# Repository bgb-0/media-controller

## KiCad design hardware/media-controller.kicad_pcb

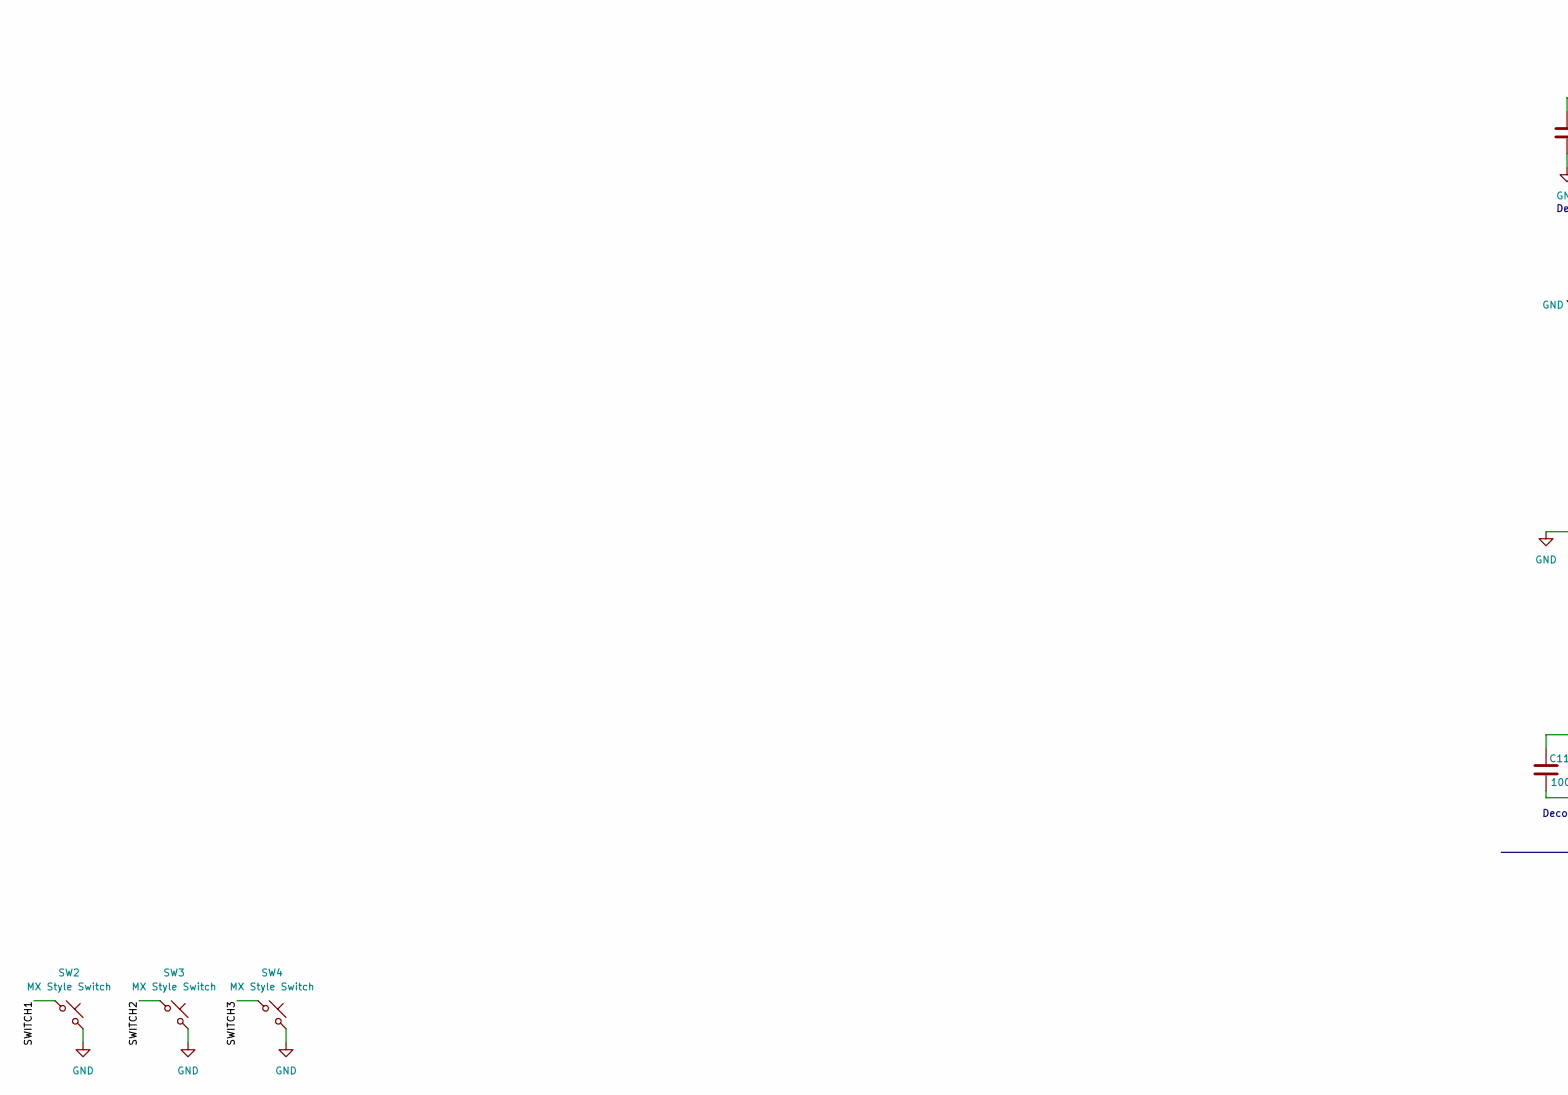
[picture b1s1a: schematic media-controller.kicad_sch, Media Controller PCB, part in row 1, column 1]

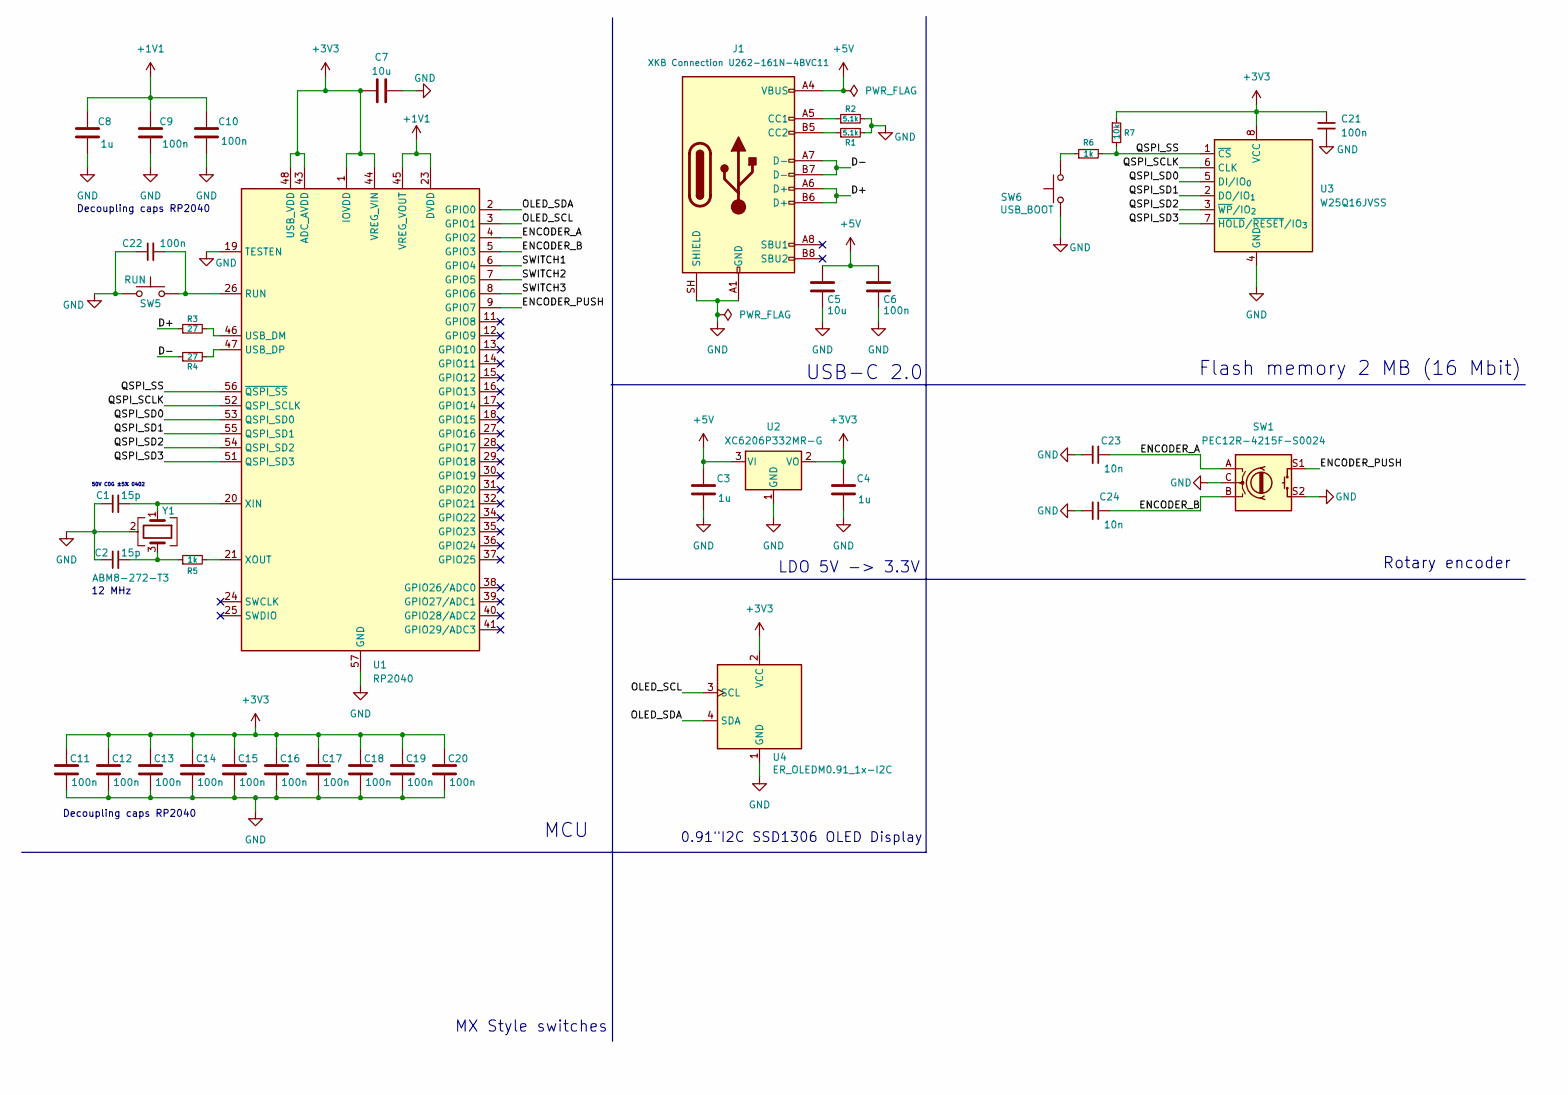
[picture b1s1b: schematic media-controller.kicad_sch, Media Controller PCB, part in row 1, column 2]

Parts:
C1, C2: 15p; C_0402_1005Metric_Pad0.74x0.62mm_HandSolder
C3, C4: 1u; C_0805_2012Metric_Pad1.18x1.45mm_HandSolder
C5, C7: 10u; C_0805_2012Metric_Pad1.18x1.45mm_HandSolder
C6, C9, C10, C11, C12, C13, C14, C15, C16, C17, C18, C19, C20, C21, C22: 100n; C_0402_1005Metric_Pad0.74x0.62mm_HandSolder
C8: 1u; C_0603_1608Metric_Pad1.08x0.95mm_HandSolder
C23, C24: 10n; C_0402_1005Metric_Pad0.74x0.62mm_HandSolder
J1: XKB Connection U262-161N-4BVC11; USB_C_Receptacle_XKB_U262-16XN-4BVC11
R1, R2: 5.1k; R_0603_1608Metric_Pad0.98x0.95mm_HandSolder
R3, R4: 27; R_0603_1608Metric_Pad0.98x0.95mm_HandSolder
R5, R6: 1k; R_0603_1608Metric_Pad0.98x0.95mm_HandSolder
R7: 10k
SW1: PEC12R-4215F-S0024
SW2, SW3, SW4: MX Style Switch; SW_Cherry_MX_1.00u_PCB
SW5: RUN; SW_SPST_TS-1088-xR025
SW6: USB_BOOT; SW_SPST_TS-1088-xR025
U1: RP2040; QFN-56-1EP_7x7mm_P0.4mm_EP3.2x3.2mm
U2: XC6206P332MR-G; SOT-23-3
U3: W25Q16JVSS; SOIC-8_5.3x5.3mm_P1.27mm
U4: ER_OLEDM0.91_1x-I2C
Y1: ABM8-272-T3; Crystal_SMD_Abracon_ABM8G-4Pin_3.2x2.5mm

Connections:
+1V1: C8.1, C9.1, C10.1, U1.23 (DVDD), U1.45 (VREG_VOUT), U1.50 (DVDD)
+3V3: C4.1, C7.1, C11.1, C12.1, C13.1, C14.1, C15.1, C16.1, C17.1, C18.1, C19.1, C20.1, C21.1, R7.1, U1.1 (IOVDD), U1.10 (IOVDD), U1.22 (IOVDD), U1.33 (IOVDD), U1.42 (IOVDD), U1.43 (ADC_AVDD), U1.44 (VREG_VIN), U1.48 (USB_VDD), U1.49 (IOVDD), U2.2 (VO), U3.8 (VCC), U4.2 (VCC)
+5V: C3.1, C5.1, C6.1, J1.A4 (VBUS), J1.A9 (VBUS), J1.B4 (VBUS), J1.B9 (VBUS), U2.3 (VI)
/D+: J1.A6 (D+), J1.B6 (D+), R3.1
/D-: J1.A7 (D-), J1.B7 (D-), R4.1
/ENCODER_A: C23.1, SW1.A, U1.4 (GPIO2)
/ENCODER_B: C24.1, SW1.B, U1.5 (GPIO3)
/ENCODER_PUSH: SW1.S1, U1.9 (GPIO7)
/OLED_SCL: U1.3 (GPIO1), U4.3 (SCL)
/OLED_SDA: U1.2 (GPIO0), U4.4 (SDA)
/QSPI_SCLK: U1.52 (QSPI_SCLK), U3.6 (CLK)
/QSPI_SD0: U1.53 (QSPI_SD0), U3.5 (DI/IO_{0})
/QSPI_SD1: U1.55 (QSPI_SD1), U3.2 (DO/IO_{1})
/QSPI_SD2: U1.54 (QSPI_SD2), U3.3 (~WP/IO_{2})
/QSPI_SD3: U1.51 (QSPI_SD3), U3.7 (~HOLD/~RESET/IO_{3})
/QSPI_SS: R6.2, R7.2, U1.56 (~QSPI_SS), U3.1 (~CS)
/SWITCH1: SW2.1, U1.6 (GPIO4)
/SWITCH2: SW3.1, U1.7 (GPIO5)
/SWITCH3: SW4.1, U1.8 (GPIO6)
GND: C1.1, C2.1, C3.2, C4.2, C5.2, C6.2, C7.2, C8.2, C9.2, C10.2, C11.2, C12.2, C13.2, C14.2, C15.2, C16.2, C17.2, C18.2, C19.2, C20.2, C21.2, C22.1, C23.2, C24.2, J1.A1 (GND), J1.A12 (GND), J1.B1 (GND), J1.B12 (GND), J1.SH (SHIELD), R1.2, R2.2, SW1.C, SW1.S2, SW2.2, SW3.2, SW4.2, SW5.1, SW6.1, U1.19 (TESTEN), U1.57 (GND), U2.1 (GND), U3.4 (GND), U4.1 (GND), Y1.2 (G), Y1.4 (G)
unnamed: C2.2, R5.1, Y1.3
unnamed: J1.A5 (CC1), R2.1
unnamed: J1.B5 (CC2), R1.1
unnamed: R6.1, SW6.2
unnamed: C22.2, SW5.2, U1.26 (RUN)
unnamed: R3.2, U1.46 (USB_DM)
unnamed: R4.2, U1.47 (USB_DP)
unnamed: C1.2, U1.20 (XIN), Y1.1
unnamed: R5.2, U1.21 (XOUT)

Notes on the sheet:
MCU
LDO 5V -> 3.3V
USB-C 2.0
50V C0G ±5% 0402
Decoupling caps RP2040
12 MHz
0.91"I2C SSD1306 OLED Display
Flash memory 2 MB (16 Mbit)
MX Style switches
Rotary encoder

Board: 2 copper layers, 42 parts (0 on the bottom side), 29 nets, no tracks yet.
